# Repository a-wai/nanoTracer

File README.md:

# nanoTracer
nanoTracer is a basic curve tracer for vacuum tubes. It uses an Arduino for its brain and a simple analog circuit provides measurements command and amplification.

## Dependencies
In order to build this software, you need the following packages :

- GNU make
- avr-gcc
- avr-libc
- avr-binutils
- avrdude

These can be obtained by typing the following command on Debian or Ubuntu systems :

`sudo apt-get install avr-gcc avr-libc avr-binutils avrdude`

## Building nanoTracer
Simply `cd` into the `nanoTracer` directory and use the `make` command.

## Uploading nanoTracer to your device
nanoTracer is compatible with Arduino boards. Once the software has been built, simply type `make upload` to write the software to your device.

When using the AVR Dragon programmer, you need to modify a few variables in the Makefile :

- `PROGRAMMER	= dragon_isp`
- `PROG_PORT	= usb`

## Usage
The Arduino needs to be connected to a computer through USB. The use of a serial terminal, such as `minicom` or `Putty` is required, with a baudrate of 500kbps.

With minicom, use the command `minicom -D /dev/ttyACM0 -b 500000 -o -w`, and make sure to disable software and hardware flow control.

Once the Arduino is ready, it should ouput the string `Starting...`. You can then select the tube type you want to measure by typing its number in the serial terminal window :

- `1` for an ECC81
- `2` for an ECC82
- `3` for an ECC83
- `8` for an ECC88
- `9` for an ECC99

The measure is started by typing `#` in the serial terminal or pressing the hardware button connected to pin D2. The Arduino then outputs a list of measures of the form :

```
Vg = 20
57,1
76,1
92,2
108,5
...
```

Each `Vg = ` line indicates the grid voltage used for this measurement. It is expressed in tenths of volts, for instance, `Vg = 20` means the grid voltage is -2V.

The following lines are the measurements in CSV format, the first value being the anode voltage in V, and the second value being the anode current in tenths of milliamperes. Thus, the line `92,2` means the tube was drawing 0.2mA when the anode voltage was 92V (and the grid voltage -2V). You can then copy/paste these lines in your favorite spreadsheet to exploit the measurements (see the example LibreOffice file in the `spreadsheet/` directory).

## Harware
nanoTracer is a DIY project. You will find all the information needed to build your own tracer under the `kicad/` directory.

## License
Source code for the software is distributed under the GNU GPL v3 license. Please see the COPYING.software file or [the GNU website](http://www.gnu.org/licenses/#GPL) for details.

Hardware design files are distributed under the CERN Open Hardware Licence v1.2. Please see the COPYING.hardware file or [the Open Hardware Repository website](http://www.ohwr.org/licenses/cern-ohl/v1.2) for details.

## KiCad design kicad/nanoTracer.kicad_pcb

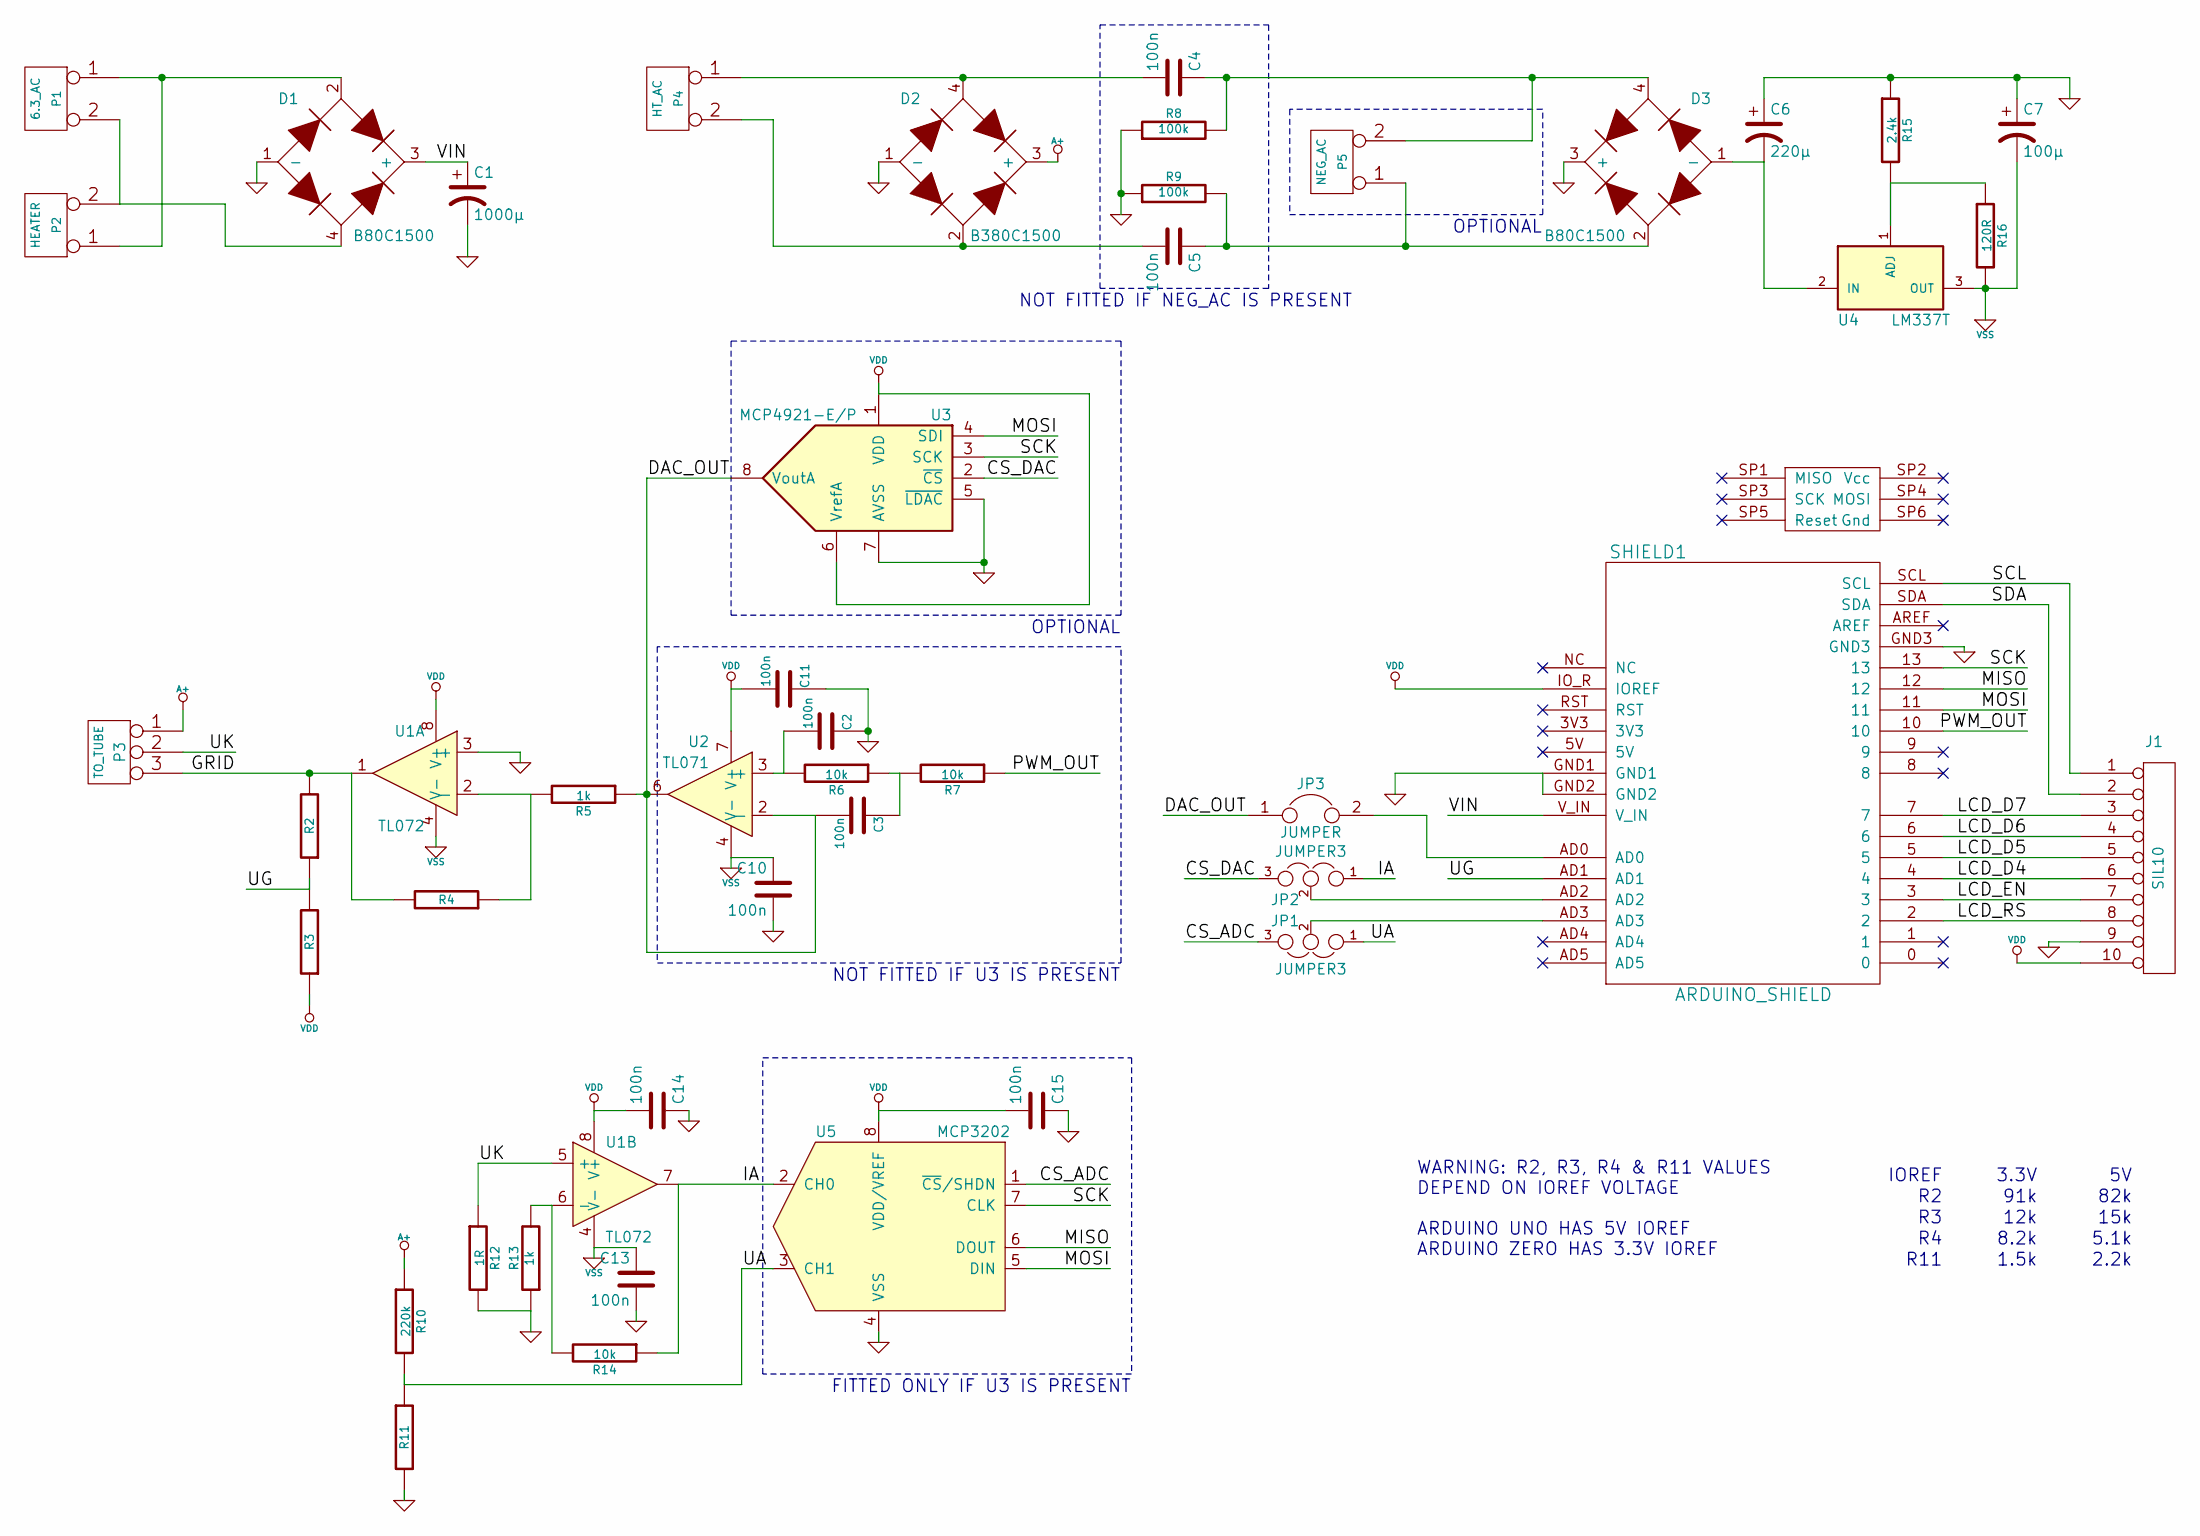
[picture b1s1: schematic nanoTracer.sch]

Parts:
C1: 1000µ; C_Radial_D10_L16_P5
C2, C3, C10, C11, C13, C14, C15: 100n; C_Rect_L7_W2_P5
C4, C5: 100n; C_Rect_L18_W6_H12_P15
C6: 220µ; C_Radial_D7.5_L11.2_P2.5
C7: 100µ; C_Radial_D6.3_L11.2_P2.5
D1, D3: B80C1500; bridge_wob
D2: B380C1500; bridge_wob
J1: SIL10; Pin_Header_Straight_1x10
JP1, JP2: JUMPER3; Pin_Header_Straight_1x03
JP3: JUMPER; SJ_OPEN
P1: 6.3_AC; bornier2
P2: HEATER; bornier2
P3: TO_TUBE; bornier3
P4: HT_AC; bornier2
P5: NEG_AC; bornier2
R2: R2; Resistor_Horizontal_RM10mm
R3: R3; Resistor_Horizontal_RM10mm
R4: R4; Resistor_Horizontal_RM10mm
R5, R13: 1k; Resistor_Horizontal_RM10mm
R6, R7, R14: 10k; Resistor_Horizontal_RM10mm
R8, R9: 100k; Resistor_Horizontal_RM10mm
R10: 220k; Resistor_Horizontal_RM10mm
R11: R11; Resistor_Horizontal_RM10mm
R12: 1R; Resistor_Horizontal_RM10mm
R15: 2.4k; Resistor_Horizontal_RM10mm
R16: 120R; Resistor_Horizontal_RM10mm
SHIELD1: ARDUINO_SHIELD
U1: TL072; DIP-8_W7.62mm_LongPads
U2: TL071; DIP-8_W7.62mm_LongPads
U3: MCP4921-E/P; DIP-8_W7.62mm_LongPads
U4: LM337T; TO-220_Neutral123_Vertical
U5: MCP3202; DIP-8_W7.62mm_LongPads

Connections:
/CS_ADC: JP1.3, U5.1 (~CS~/SHDN)
/CS_DAC: JP2.3, U3.2 (~CS~)
/DAC_OUT: C3.2, JP3.1, R5.1, U2.2 (-), U2.6, U3.8 (VoutA)
/GRID: P3.3, R2.2, R4.2, U1.1
/IA: JP2.1, R14.1, U1.7, U5.2 (CH0)
/LCD_D4: J1.6, SHIELD1.4
/LCD_D5: J1.5, SHIELD1.5
/LCD_D6: J1.4, SHIELD1.6
/LCD_D7: J1.3, SHIELD1.7
/LCD_EN: J1.7, SHIELD1.3
/LCD_RS: J1.8, SHIELD1.2
/MISO: SHIELD1.12, U5.6 (DOUT)
/MOSI: SHIELD1.11, U3.4 (SDI), U5.5 (DIN)
/PWM_OUT: R7.1, SHIELD1.10
/SCK: SHIELD1.13, U3.3 (SCK), U5.7 (CLK)
/SCL: J1.1, SHIELD1.SCL
/SDA: J1.2, SHIELD1.SDA
/UA: JP1.1, R10.2, R11.1, U5.3 (CH1)
/UG: R2.1, R3.2, SHIELD1.AD1
/UK: P3.2, R12.1, U1.5 (+)
/VIN: C1.1, D1.3 (+), SHIELD1.V_IN
A+: D2.3 (+), P3.1, R10.1
GND: C1.2, C2.1, C6.1, C7.1, C10.2, C11.1, C13.2, C14.1, C15.1, D1.1 (-), D2.1 (-), D3.3 (+), J1.9, R8.1, R9.1, R11.2, R12.2, R13.1, R15.1, SHIELD1.GND1, SHIELD1.GND2, SHIELD1.GND3, U1.3 (+), U3.5 (~LDAC~), U3.7 (AVSS), U5.4 (VSS)
unnamed: C2.2, R6.2, U2.3 (+)
unnamed: C3.1, R6.1, R7.2
unnamed: C4.1, D3.4, P5.2 (PM), R8.2
unnamed: C4.2, D2.4, P4.1
unnamed: C5.1, D3.2, P5.1, R9.2
unnamed: C5.2, D2.2, P4.2 (PM)
unnamed: C6.2, D3.1 (-), U4.2 (IN)
unnamed: D1.2, P1.1, P2.1
unnamed: D1.4, P1.2 (PM), P2.2 (PM)
unnamed: JP1.2, SHIELD1.AD3
unnamed: JP2.2, SHIELD1.AD2
unnamed: JP3.2, SHIELD1.AD0
unnamed: R4.1, R5.2, U1.2 (-)
unnamed: R13.2, R14.2, U1.6 (-)
unnamed: R15.2, R16.1, U4.1 (ADJ)
VDD: C11.2, C14.2, C15.2, J1.10, R3.1, SHIELD1.IO_R (IOREF), U1.8 (V+), U2.7 (V+), U3.1 (VDD), U3.6 (VrefA), U5.8 (VDD/VREF)
VSS: C7.2, C10.1, C13.1, R16.2, U1.4 (V-), U2.4 (V-), U4.3 (OUT)

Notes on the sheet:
NOT FITTED IF U3 IS PRESENT
NOT FITTED IF NEG_AC IS PRESENT
FITTED ONLY IF U3 IS PRESENT
OPTIONAL
IOREF
R11
3.3V
82k
15k
5.1k
2.2k
1.5k
8.2k
12k
91k
WARNING: R2, R3, R4 & R11 VALUES DEPEND ON IOREF VOLTAGE ARDUINO UNO HAS 5V IOREF ARDUINO ZERO HAS 3.3V IOREF

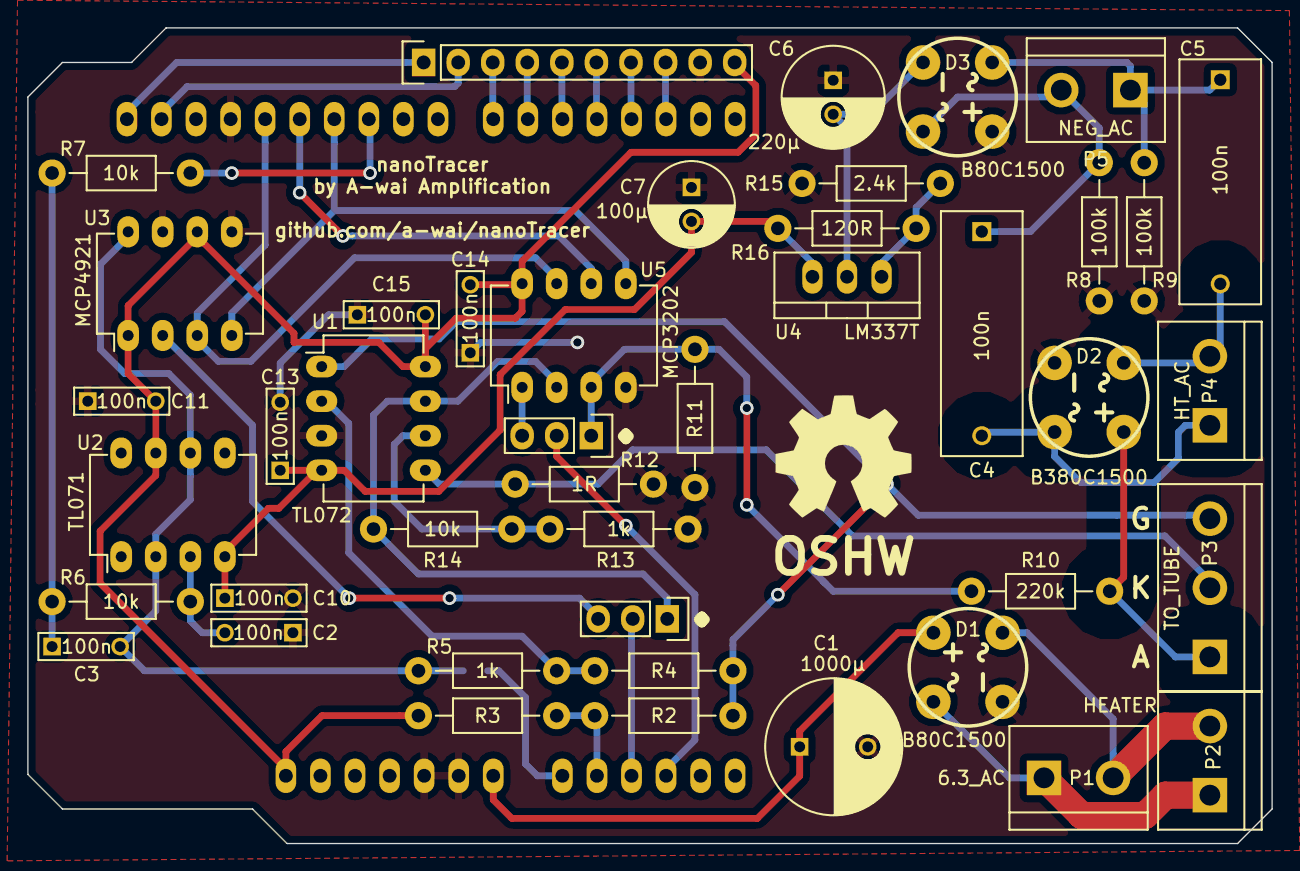
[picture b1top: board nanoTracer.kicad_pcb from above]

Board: 2 copper layers, 91.4 x 59.9 mm, 46 parts (0 on the bottom side), 40 nets.

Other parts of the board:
LOGO_OSHW_silkscreen_10mm: val**; LOGO_OSHW_silkscreen_10mm

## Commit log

2015-02-28 Initial import
2015-02-28 Clean source tree
2015-02-28 Add Eclipse project files
2015-02-28 Add KiCAD files & LibreOffice example spreadsheet
2015-02-28 Ignore KiCaD backup file
2015-02-28 Add KiCAD cache libraries
2015-02-28 Correct indentation
2015-02-28 Modify code organization
2015-02-28 Correct Makefile indentation
2015-02-28 Makefile indentation
2015-08-25 Correct formatting on README.md
2016-07-19 Start modular Arduino shield project
2016-07-19 Use SCL/SDA pins for buttons to ease routing
2016-07-19 Complete footprints association
2016-07-19 Update schematics PDF
2016-07-19 Fix incorrect frame on schematics
2016-07-19 [SCH] Move BTN_UP/BTN_DN as not connected on Arduino Zero
2016-07-22 Switch to 10-pin header w/I2C for expansion port
2016-07-22 Update PDF schematic
2016-07-24 First PCB version
2016-07-24 Fix diode bridges footprints in PCB
2016-07-24 Fix vias diameter & remove unused pin
2016-07-26 Optimize routing & silkscreen
2016-08-01 Added headers for unconnected Arduino pins
2016-08-01 Update licence files
2016-08-01 Improve COPYING.hardware formatting
2016-08-22 Add BOM
